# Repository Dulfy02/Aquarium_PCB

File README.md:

# Tank_Refillerator_PCB
A continuation of my Aquarium Refillerator incorporated into an intgegrated PCB system. The provided links describe the purpose of this project in greater detail. The PCB will be a shield-like pluggable that will encompase the prototype project.

links to the prototype github and hackster pages
  https://github.com/Dulfy02/ENGI301/tree/master/Aquarium_Pump
  https://www.hackster.io/amadoradulfo/tank-refillerator-69f6fc

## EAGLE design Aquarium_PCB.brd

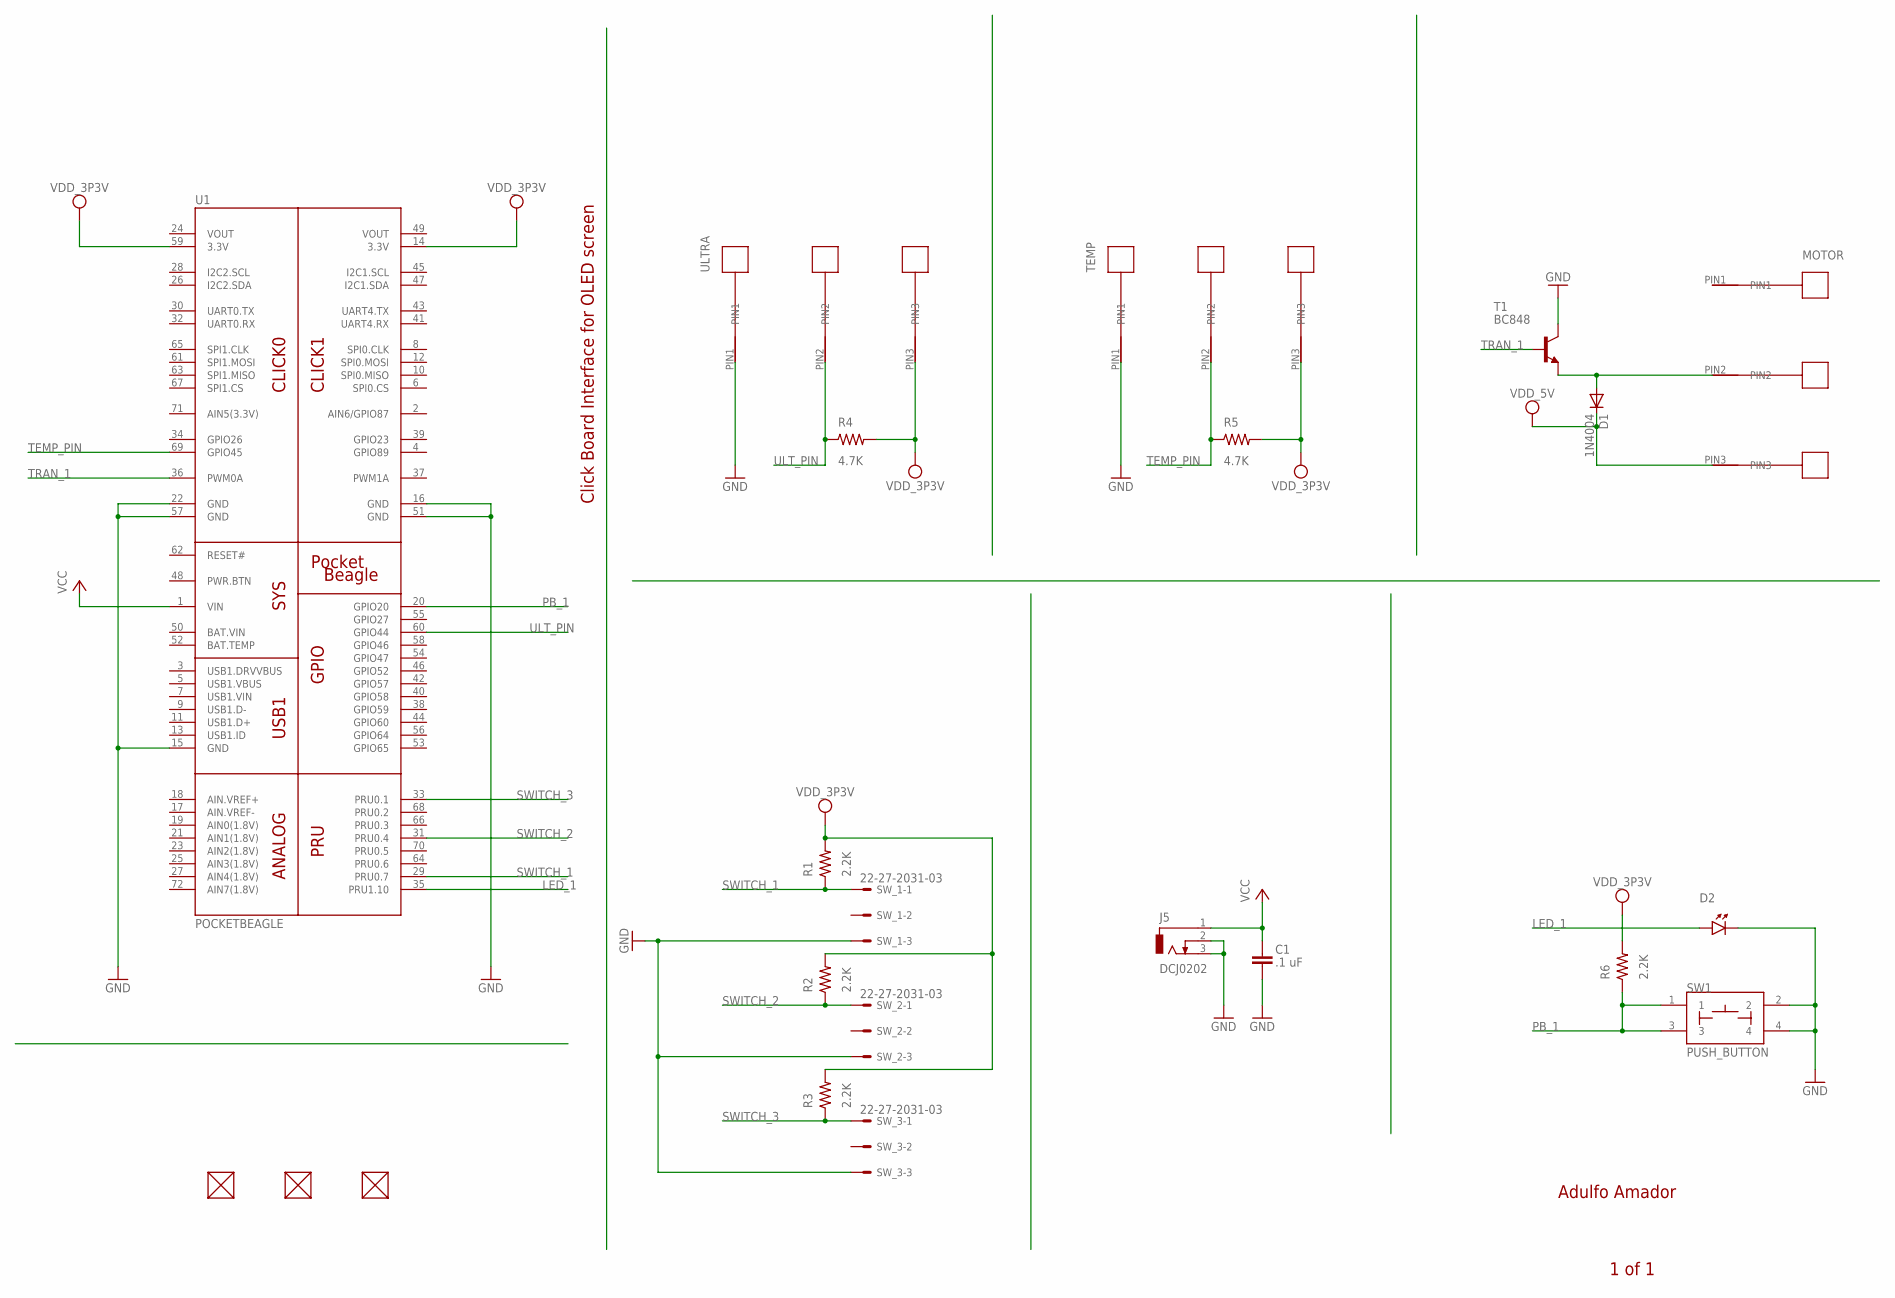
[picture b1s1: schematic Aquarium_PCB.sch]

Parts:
C1: .1 uF; C0603
D1: 1N4004; DO41-10
D2: LTST-C191TBKT; LED
FUD1, FUD2, FUD3: FIDUCIAL; FIDUCIAL_40MIL
J5: DCJ0202
MOTOR: BM03B-AUHKS-GA-TB; AUXILIARY_CONNECTOR
R1, R2, R3, R6: 2.2K; R0603
R4, R5: 4.7K; R0603
SW1: PUSH_BUTTON; BUTTON_12.5MM
SW_1, SW_2, SW_3: 22-27-2031-03; 6410-03
T1: BC848; SOT23
TEMP: BM03B-AUHKS-GA-TB; AUXILIARY_CONNECTOR
U1: POCKETBEAGLE
ULTRA: BM03B-AUHKS-GA-TB; AUXILIARY_CONNECTOR

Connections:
BAT.VIN: U1.50 (BAT.VIN)
GND: C1.2, D2.C, J5.2, J5.3, SW1.2, SW1.4, SW_1.3, SW_2.3, SW_3.3, T1.3 (C), TEMP.PIN1, U1.15 (GND), U1.16 (GND), U1.22 (GND), U1.51 (GND), U1.57 (GND), ULTRA.PIN1
GND_MOTOR: D1.A, MOTOR.PIN2, T1.2 (E)
LED_1: D2.A, U1.35 (PRU1.10)
PB_1: R6.1, SW1.1, SW1.3, U1.20 (GPIO20)
PWR_MOTOR: D1.C, MOTOR.PIN3
SWITCH_1: R1.1, SW_1.1, U1.29 (PRU0.7)
SWITCH_2: R2.1, SW_2.1, U1.31 (PRU0.4)
SWITCH_3: R3.1, SW_3.1, U1.33 (PRU0.1)
TEMP_PIN: R5.1, TEMP.PIN2, U1.69 (GPIO45)
TRAN_1: T1.1 (B), U1.36 (PWM0A)
ULT_PIN: R4.1, U1.60 (GPIO44), ULTRA.PIN2
VCC: C1.1, J5.1, U1.1 (VIN)
VDD_3P3V: R1.2, R2.2, R3.2, R4.2, R5.2, R6.2, TEMP.PIN3, U1.14 (3.3V), U1.59 (3.3V), ULTRA.PIN3
VOUT: U1.24 (VOUT), U1.49 (VOUT)

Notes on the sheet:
Adulfo Amador
1 of 1
Click Board Interface for OLED screen

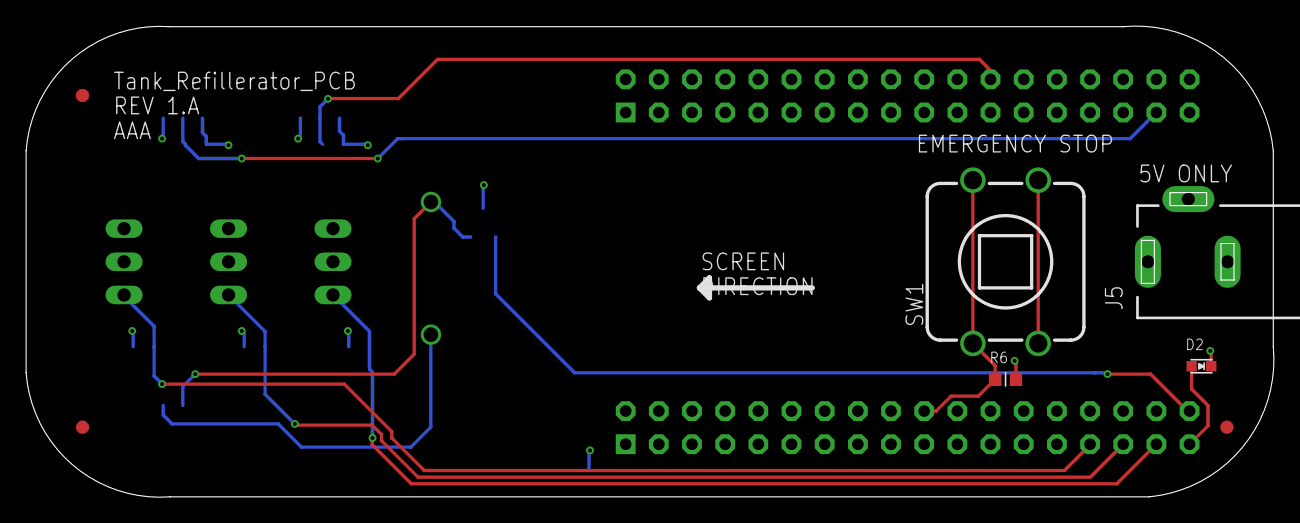
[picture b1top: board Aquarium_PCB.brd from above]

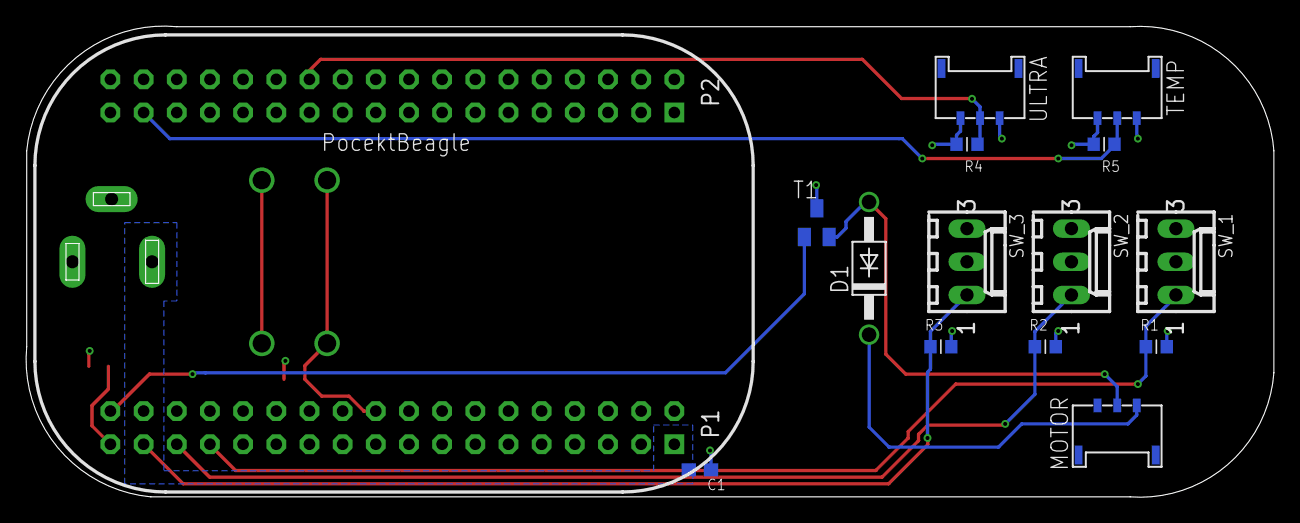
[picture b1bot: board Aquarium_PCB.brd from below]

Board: 4 copper layers, 95.5 x 36.1 mm, 22 parts (14 on the bottom side), 14 nets.

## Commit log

2018-12-12 Create empty
